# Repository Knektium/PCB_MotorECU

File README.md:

Wolley Motor ECU
================

This is the KiCad project for the PCB that is used as ECU for the Wolley Wheel
and Fan modules.

It's a circular PCB that a brushed DC motor can be directly mounted on to be
controlled by the driver and MCU onboard through CAN.

Specifications
--------------

| Name                       | Value    |
| -------------------------- | -------- |
| PCB layers                 | 2        |
| PCB diameter               | 61 mm    |
| Max motor diameter         | 28 mm    |
| Motor center hole diameter | 10 mm    |
| Motor voltage              | 6 - 36 V |
| Max motor current          | 6 A      |
| Control Interface          | CAN      |

Key Components
--------------

| Component | Part | Details |
| --------- | ---- | ------- |
| MCU | Infineon XMC1404_F064X200A | ARM Cortex-M0, 32-bit, 48 MHz, 200 kB flash |
| Motor driver | Infineon IFX9201SG | 6 A and 36 V H-bridge with SPI diagnostics |
| CAN transceiver | Infineon TLE7251VSJ | |
| Speed sensor | Infineon TLE4964-4M | High precision unipolar hall effect switch |
| Temperature sensor | TI LM35DM | Precision centigrade temperature sensor |

Motor Alternatives
------------------

 - Mabuchi RS-385PV-2465
 - Mabuchi RS-365

Release Notes
-------------

Version 1.4:
 - Replaced the 4-pin connector with the new 5-pin connector.
 - Removed the battery power connector.

Version 1.3:
 - Moved the connectors closer to the middle to allow for more space and
   therefore better mounting.
 - Added a key hole to prevent the PCB from spinning when used as the
   CentrifugalFan ECU.
 - Joined the mount holes with the motor hole.
 - Smaller silk screen improvements.

Version 1.2 (same as CentrifugalFanECU v1.0):
 - Added a dedicated connector for the motor power.
 - Added a temperature sensor.
 - Added a status LED.
 - Removed two of the mount holes.
 - Made the motor hole bigger to fit a Mabuchi RS-380.

Version 1.1:
 - Replaced the motor driver with a better one that can handle up to 36 V.
 - Other improvements.

Licence
-------

Licenced under the CERN Open Hardware Licence v1.2.

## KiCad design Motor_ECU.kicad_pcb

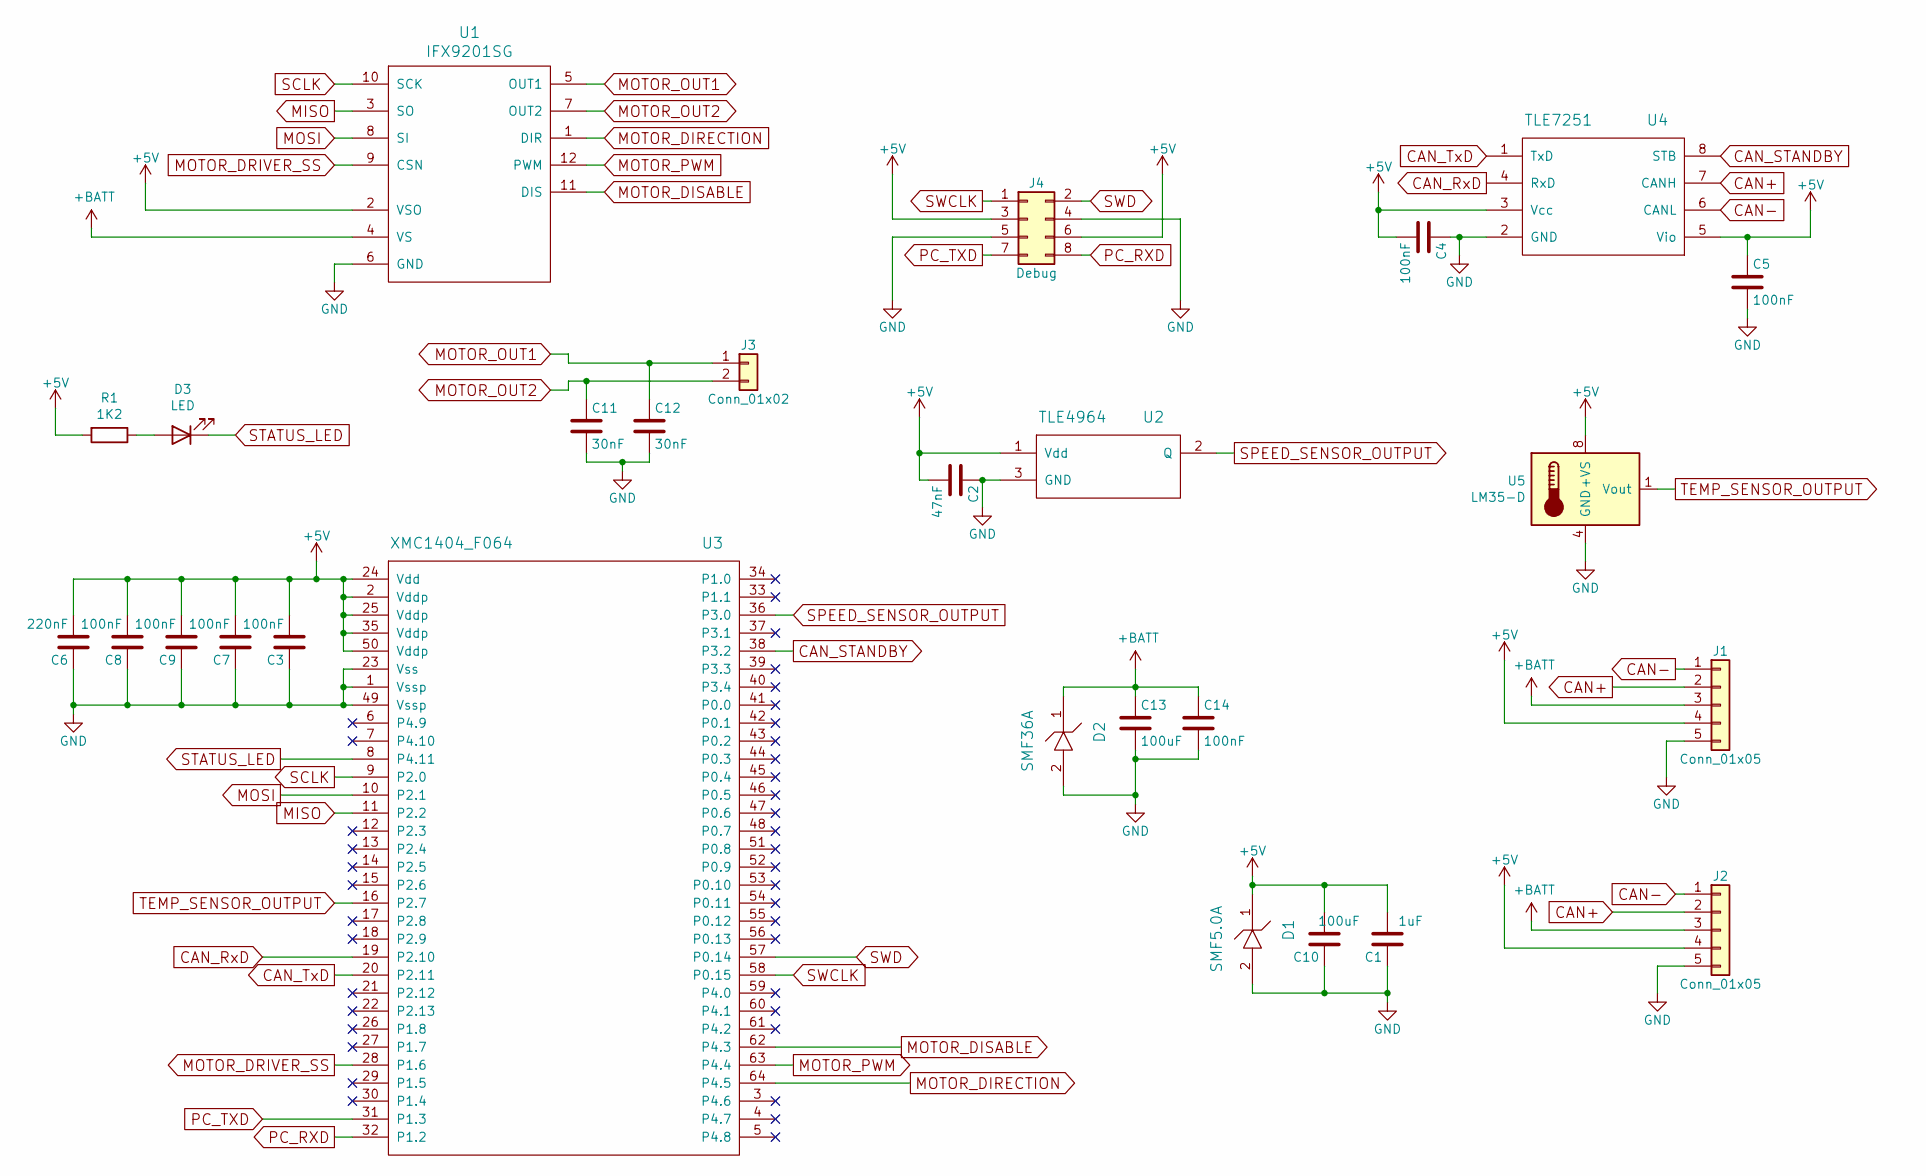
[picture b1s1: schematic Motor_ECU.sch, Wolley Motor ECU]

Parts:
C1: 1uF; C_0805_HandSoldering
C2: 47nF; C_0805_HandSoldering
C3, C4, C5, C7, C8, C9, C14: 100nF; C_0805_HandSoldering
C6: 220nF; C_0805_HandSoldering
C10, C13: 100uF; C_0805_HandSoldering
C11, C12: 30nF; C_0805_HandSoldering
D1: SMF5.0A; D_SOD-123F
D2: SMF36A; D_SOD-123F
D3: LED; C_0805_HandSoldering
J1, J2: Conn_01x05; PinHeader_1x05_P2.54mm_Vertical
J3: Conn_01x02; PinHeader_1x02_P2.54mm_Vertical
J4: Debug; Pin_Header_Straight_2x04_Pitch2.54mm_SMD
R1: 1K2; C_0805_HandSoldering
U1: IFX9201SG; SOIC-12_HeatSlugs
U2: TLE4964; TSOT-23_HandSoldering
U3: XMC1404_F064; TQFP-64_10x10mm_Pitch0.5mm_Handsoldering
U4: TLE7251; SOIC-8_3.9x4.9mm_Pitch1.27mm
U5: LM35-D; SOIC-8_3.9x4.9mm_P1.27mm

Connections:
+5V: C1.2, C2.2, C3.2, C4.2, C5.1, C6.2, C7.2, C8.2, C9.2, C10.2, D1.1, J1.4, J2.4, J4.3, J4.6, R1.2, U1.2 (VSO), U2.1 (Vdd), U3.2 (Vddp), U3.24 (Vdd), U3.25 (Vddp), U3.35 (Vddp), U3.50 (Vddp), U4.3 (Vcc), U4.5 (Vio), U5.8 (+VS)
+BATT: C13.1, C14.1, D2.1, J1.3, J2.3, U1.4 (VS)
CAN+: J1.2, J2.2, U4.7 (CANH)
CAN-: J1.1, J2.1, U4.6 (CANL)
CAN_RxD: U3.19 (P2.10), U4.4 (RxD)
CAN_STANDBY: U3.38 (P3.2), U4.8 (STB)
CAN_TxD: U3.20 (P2.11), U4.1 (TxD)
GND: C1.1, C2.1, C3.1, C4.1, C5.2, C6.1, C7.1, C8.1, C9.1, C10.1, C11.2, C12.2, C13.2, C14.2, D1.2, D2.2, J1.5, J2.5, J4.4, J4.5, U1.6 (GND), U2.3 (GND), U3.1 (Vssp), U3.23 (Vss), U3.49 (Vssp), U4.2 (GND), U5.4 (GND)
MISO: U1.3 (SO), U3.11 (P2.2)
MOSI: U1.8 (SI), U3.10 (P2.1)
MOTOR_DIRECTION: U1.1 (DIR), U3.64 (P4.5)
MOTOR_DISABLE: U1.11 (DIS), U3.62 (P4.3)
MOTOR_DRIVER_SS: U1.9 (CSN), U3.28 (P1.6)
MOTOR_OUT1: C12.1, J3.1, U1.5 (OUT1)
MOTOR_OUT2: C11.1, J3.2, U1.7 (OUT2)
MOTOR_PWM: U1.12 (PWM), U3.63 (P4.4)
unnamed: D3.2 (A), R1.1
PC_RXD: J4.8, U3.32 (P1.2)
PC_TXD: J4.7, U3.31 (P1.3)
SCLK: U1.10 (SCK), U3.9 (P2.0)
SPEED_SENSOR_OUTPUT: U2.2 (Q), U3.36 (P3.0)
STATUS_LED: D3.1 (K), U3.8 (P4.11)
SWCLK: J4.1, U3.58 (P0.15)
SWD: J4.2, U3.57 (P0.14)
TEMP_SENSOR_OUTPUT: U3.16 (P2.7), U5.1 (Vout)

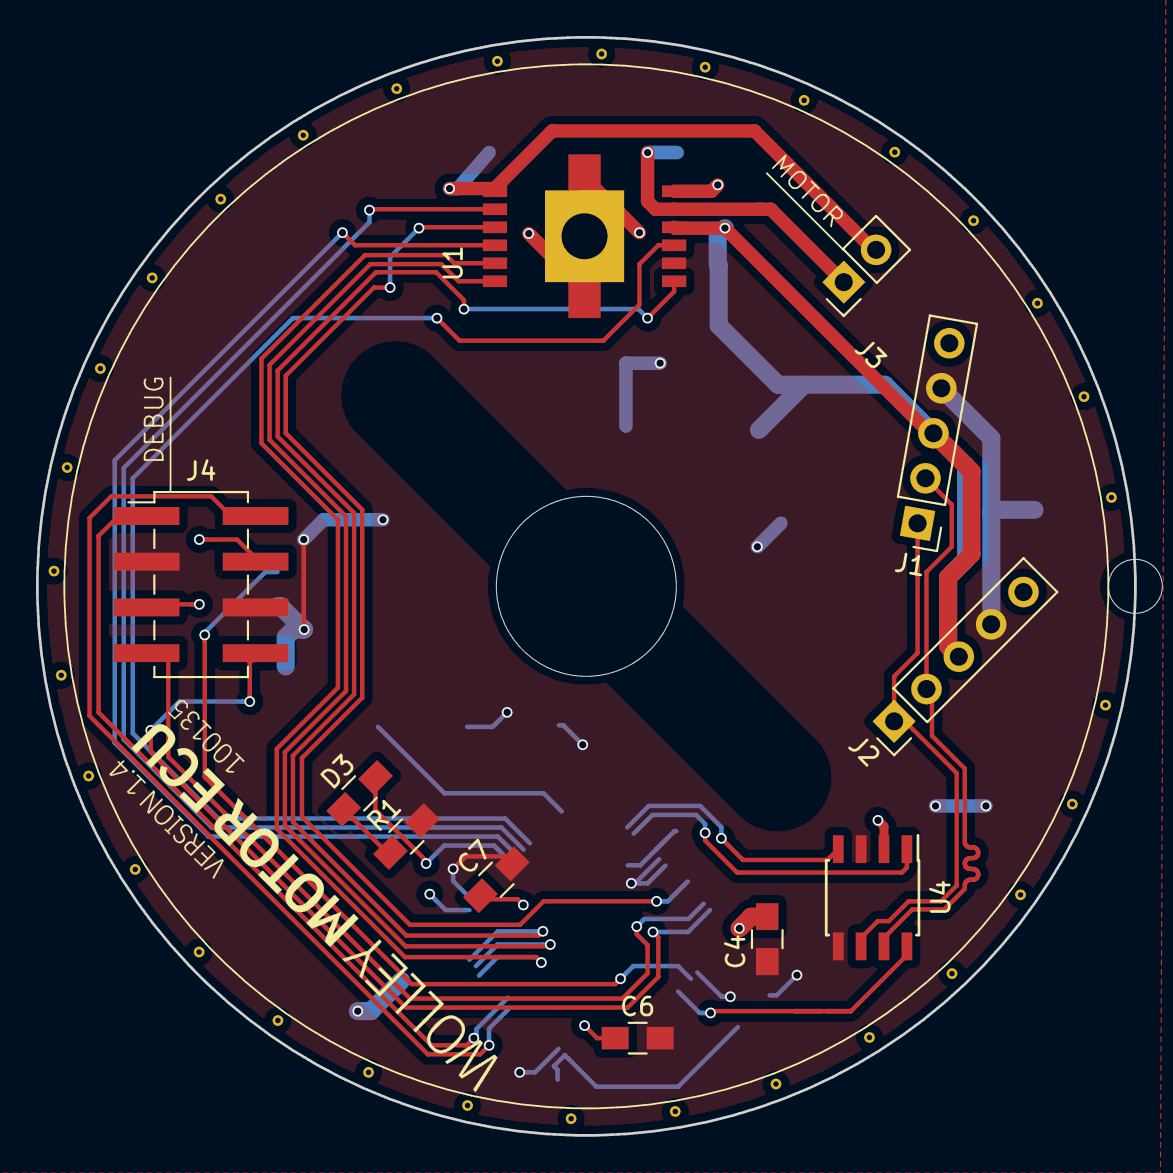
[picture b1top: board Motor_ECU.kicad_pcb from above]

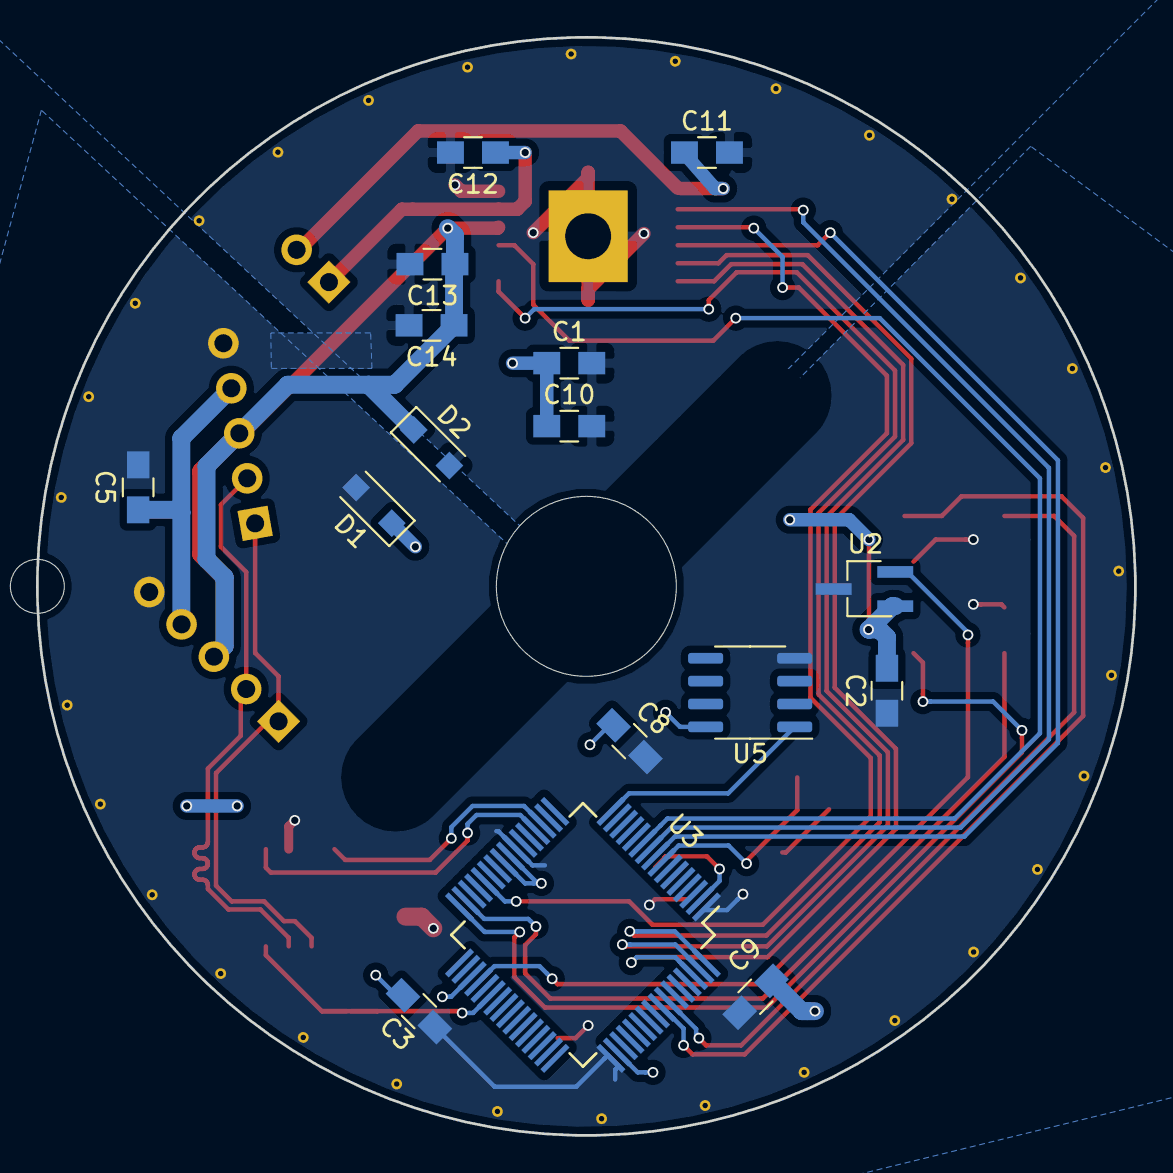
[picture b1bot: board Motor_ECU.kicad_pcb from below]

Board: 2 copper layers, 61.0 x 61.0 mm, 30 parts (16 on the bottom side), 25 nets.

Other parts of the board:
M**: Motor_Mount_Hole; Mount_Hole_M3x6.5
M**#2: Motor_Mount_Hole; Mount_Hole_M3x6.5
M**#3: Motor_Center_Hole

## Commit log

2018-12-10 Add KiCad files
2018-12-10 Add README and LICENCE files
2018-12-10 Added file extension .md to README
2018-12-10 Moved mount hole footprint files to root dir along with other footprints
2018-12-12 Add Wolley Interconnect logo footprint to local library
2020-12-07 Replace the motor driver and other improvements
2021-07-21 Copy the changes from the CentrifugalFan module
2021-07-21 Rename the schematic
2021-07-21 Change the version text on the PCB
2021-08-01 Move connectors closer to middle
2021-08-01 Smaller clean up
2021-08-01 Add key hole
2021-08-01 Join the mount holes with the motor hole
2021-08-01 Fix silk screen and texts and smaller improvements
2021-08-02 Relocate the second connector a bit and add mor space between the labels
2021-08-03 Add release notes to README file
2021-08-05 Rename the PCB to Motor ECU since it is shared between more than one module
2021-08-05 Rename the files to reflect the project name
2021-08-05 Clean up in the symbol libs
2021-08-05 Improve the format of the README file
2021-08-09 Fix the module names in the README file after the renaming
2021-08-19 Update README file
2021-10-31 Fix formatting in README
2022-02-12 Replace the 4-pin connectors with the new 5-pin connector
